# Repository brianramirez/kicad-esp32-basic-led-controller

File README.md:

# kicad-esp32-basic-led-controller

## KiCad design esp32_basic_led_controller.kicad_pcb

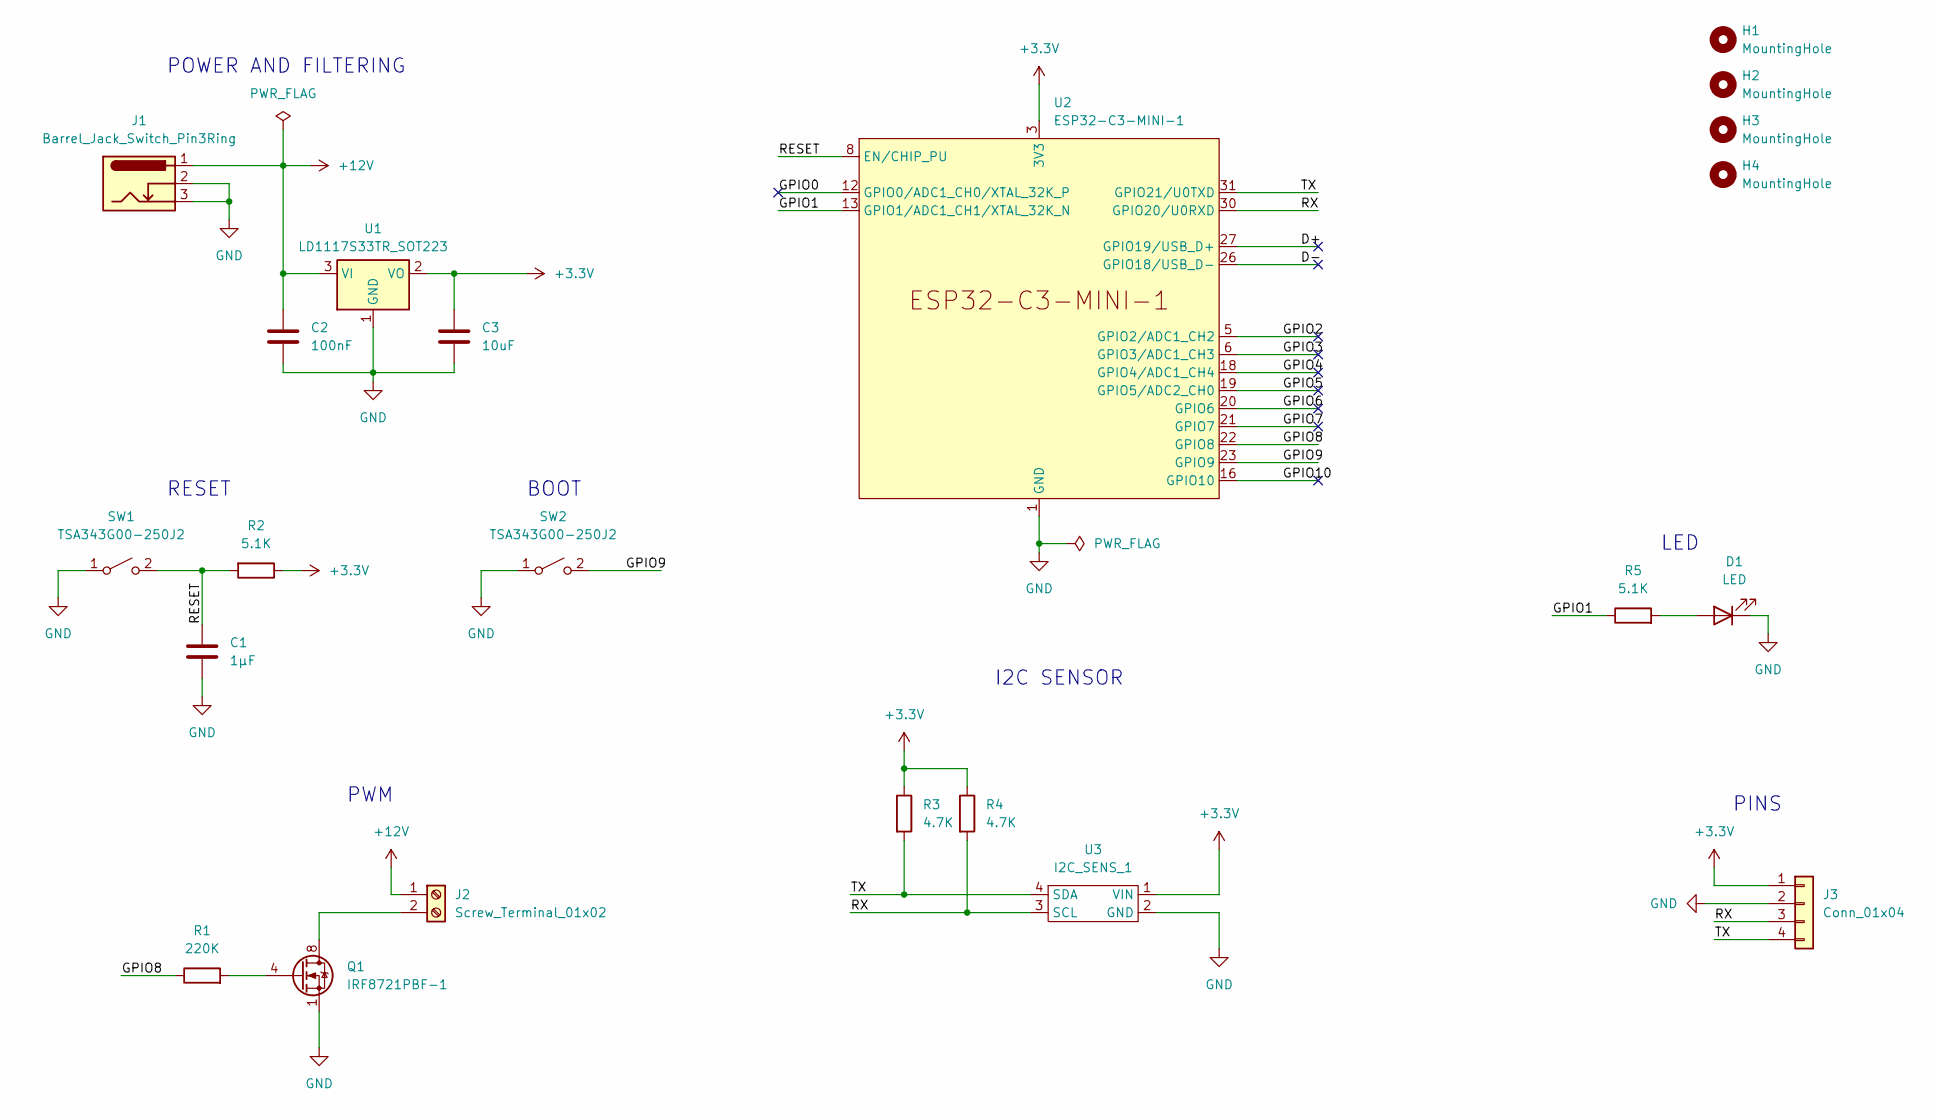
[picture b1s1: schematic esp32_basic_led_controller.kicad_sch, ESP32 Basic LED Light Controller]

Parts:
C1: 1μF; C_0603_1608Metric_Pad1.08x0.95mm_HandSolder
C2: 100nF; C_0603_1608Metric_Pad1.08x0.95mm_HandSolder
C3: 10uF; C_0805_2012Metric_Pad1.18x1.45mm_HandSolder
D1: LED; LED_0603_1608Metric_Pad1.05x0.95mm_HandSolder
H1, H2, H3, H4: MountingHole; MountingHole_2.2mm_M2_DIN965
J1: Barrel_Jack_Switch_Pin3Ring; BarrelJack_Horizontal
J2: Screw_Terminal_01x02; TerminalBlock_Phoenix_MKDS-1,5-2-5.08_1x02_P5.08mm_Horizont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
J3: Conn_01x04; PinHeader_1x04_P1.27mm_Vertical
Q1: IRF8721PBF-1; SOIC-8_3.9x4.9mm_P1.27mm
R1: 220K; R_0603_1608Metric_Pad0.98x0.95mm_HandSolder
R2, R5: 5.1K; R_0603_1608Metric_Pad0.98x0.95mm_HandSolder
R3, R4: 4.7K; R_0603_1608Metric_Pad0.98x0.95mm_HandSolder
SW1, SW2: TSA343G00-250J2
U1: LD1117S33TR_SOT223; SOT-223-3_TabPin2
U2: ESP32-C3-MINI-1
U3: I2C_SENS_1; PinSocket_1x04_P1.27mm_Vertical

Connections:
+3.3V: C3.1, J3.1, R2.1, R3.1, R4.1, U1.2 (VO), U2.3 (3V3), U3.1 (VIN)
+12V: C2.1, J1.1, J2.1, U1.3 (VI)
/D+: U2.27 (GPIO19/USB_D+)
/D-: U2.26 (GPIO18/USB_D-)
/GPIO0: U2.12 (GPIO0/ADC1_CH0/XTAL_32K_P)
/GPIO1: R5.1, U2.13 (GPIO1/ADC1_CH1/XTAL_32K_N)
/GPIO2: U2.5 (GPIO2/ADC1_CH2)
/GPIO3: U2.6 (GPIO3/ADC1_CH3)
/GPIO4: U2.18 (GPIO4/ADC1_CH4)
/GPIO5: U2.19 (GPIO5/ADC2_CH0)
/GPIO6: U2.20 (GPIO6)
/GPIO7: U2.21 (GPIO7)
/GPIO8: R1.1, U2.22 (GPIO8)
/GPIO9: SW2.2 (B), U2.23 (GPIO9)
/GPIO10: U2.16 (GPIO10)
/RESET: C1.1, R2.2, SW1.2 (B), U2.8 (EN/CHIP_PU)
/RX: J3.3, R4.2, U2.30 (GPIO20/U0RXD), U3.3 (SCL)
/TX: J3.4, R3.2, U2.31 (GPIO21/U0TXD), U3.4 (SDA)
GND: C1.2, C2.2, C3.2, D1.1 (K), J1.2, J1.3, J3.2, Q1.1 (S), Q1.2 (S), Q1.3 (S), SW1.1 (A), SW2.1 (A), U1.1 (GND), U2.1 (GND), U2.2 (GND), U2.11 (GND), U2.14 (GND), U2.36 (GND), U2.37 (GND), U2.38 (GND), U2.39 (GND), U2.40 (GND), U2.41 (GND), U2.42 (GND), U2.43 (GND), U2.44 (GND), U2.45 (GND), U2.46 (GND), U2.47 (GND), U2.48 (GND), U2.49 (GND), U2.50 (GND), U2.51 (GND), U2.52 (GND), U2.53 (GND), U3.2 (GND)
unnamed: D1.2 (A), R5.2
unnamed: J2.2, Q1.5 (D), Q1.6 (D), Q1.7 (D), Q1.8 (D)
unnamed: Q1.4 (G), R1.2

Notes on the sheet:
LED
PINS
BOOT
POWER AND FILTERING
PWM
I2C SENSOR
RESET

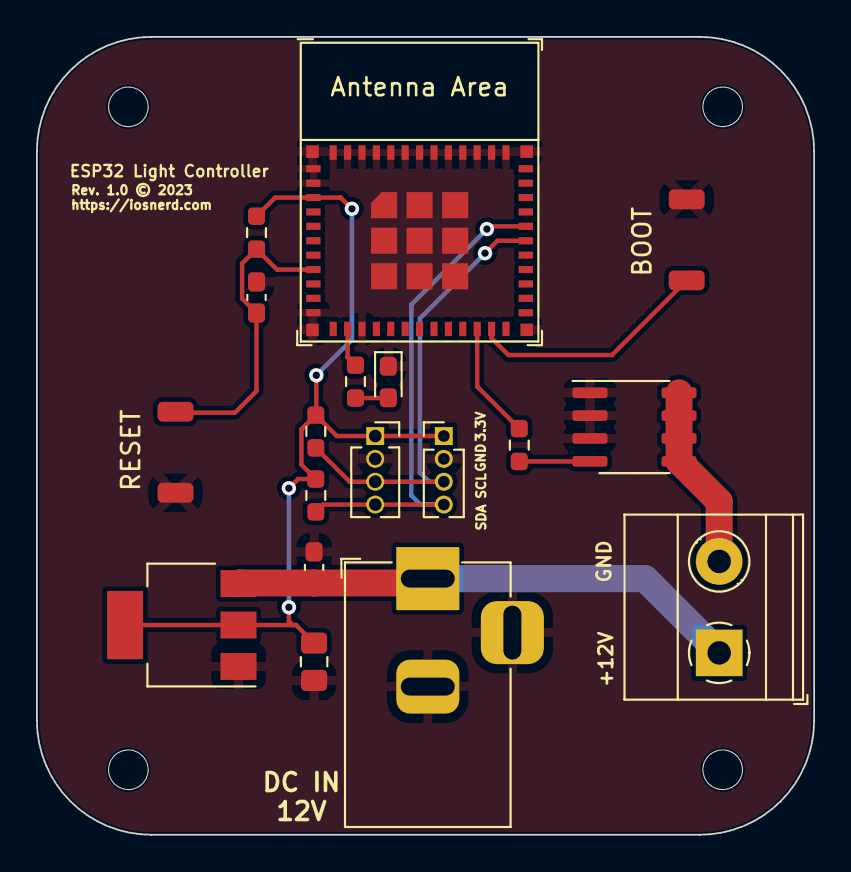
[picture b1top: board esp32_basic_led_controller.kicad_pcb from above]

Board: 2 copper layers, 43.2 x 44.3 mm, 22 parts (0 on the bottom side), 12 nets.

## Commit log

2023-08-31 Added initial project files
2023-08-31 Added LICENSE
2023-08-31 PCB layout
2023-09-01 Updated PCB layout
2023-09-02 Migrated to ESP32-C3-Mini-1 SoC
2023-09-03 Vertical board layout
2023-09-05 Board layout tweaks
2023-09-05 Finished PCB routing and layout
2023-09-05 Generated initial gerber files

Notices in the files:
esp32_basic_led_controller.kicad_pcb:
https://spdx.org/licenses/CERN-OHL-S-2.0.html
License: CERN-OHL-S-2.0
Rev. 1.0 © 2023
